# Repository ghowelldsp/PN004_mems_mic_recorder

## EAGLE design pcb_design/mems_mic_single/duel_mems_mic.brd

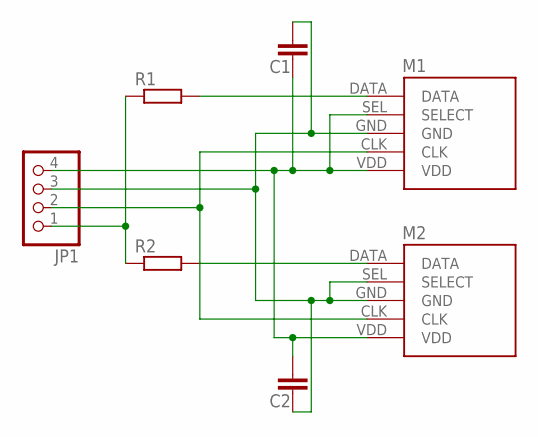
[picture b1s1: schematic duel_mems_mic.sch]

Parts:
C1, C2: C-EUC0402; C0402
JP1: PINHD-1X4; 1X04
M1, M2: MEMS_MIC_IM69D130-DS; IM69D130-DS
R1, R2: R-EU_R0402; R0402

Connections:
GND: C1.1, C2.2, JP1.3, M1.GND, M2.GND, M2.SEL (SELECT)
unnamed: M1.DATA, R1.2
unnamed: JP1.1, R1.1, R2.1
unnamed: C1.2, C2.1, JP1.4, M1.SEL (SELECT), M1.VDD, M2.VDD
unnamed: M2.DATA, R2.2
unnamed: JP1.2, M1.CLK, M2.CLK

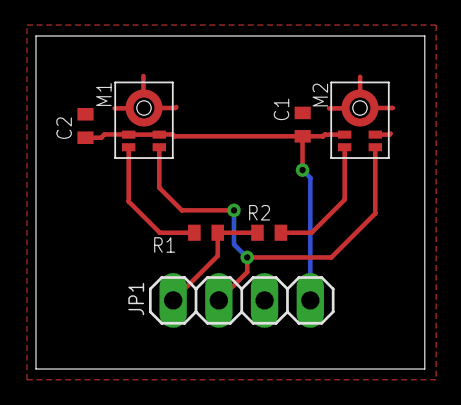
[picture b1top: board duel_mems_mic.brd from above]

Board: 2 copper layers, 21.6 x 18.5 mm, 7 parts (0 on the bottom side), 6 nets.

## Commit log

2020-10-26 created .gitignore, added *.DS_Store
2020-10-26 initial commit of main project data
    * mic measurements added to .gitignore
2020-10-26 removed old data transfer method
2020-10-26 clock output from fir decimation filter to solve timing issues
2020-10-26 removed unused system reset signal from fifo read and write
2020-11-03 set synchronous reset in biquad, added timing constraints
2020-11-03 frequency response measurements
2020-11-06 filenames update
2020-11-06 updating vivado project
2020-11-07 micRecCtl saves data as .wav, remove matlab txt2wav
2020-11-07 updated folder structure
